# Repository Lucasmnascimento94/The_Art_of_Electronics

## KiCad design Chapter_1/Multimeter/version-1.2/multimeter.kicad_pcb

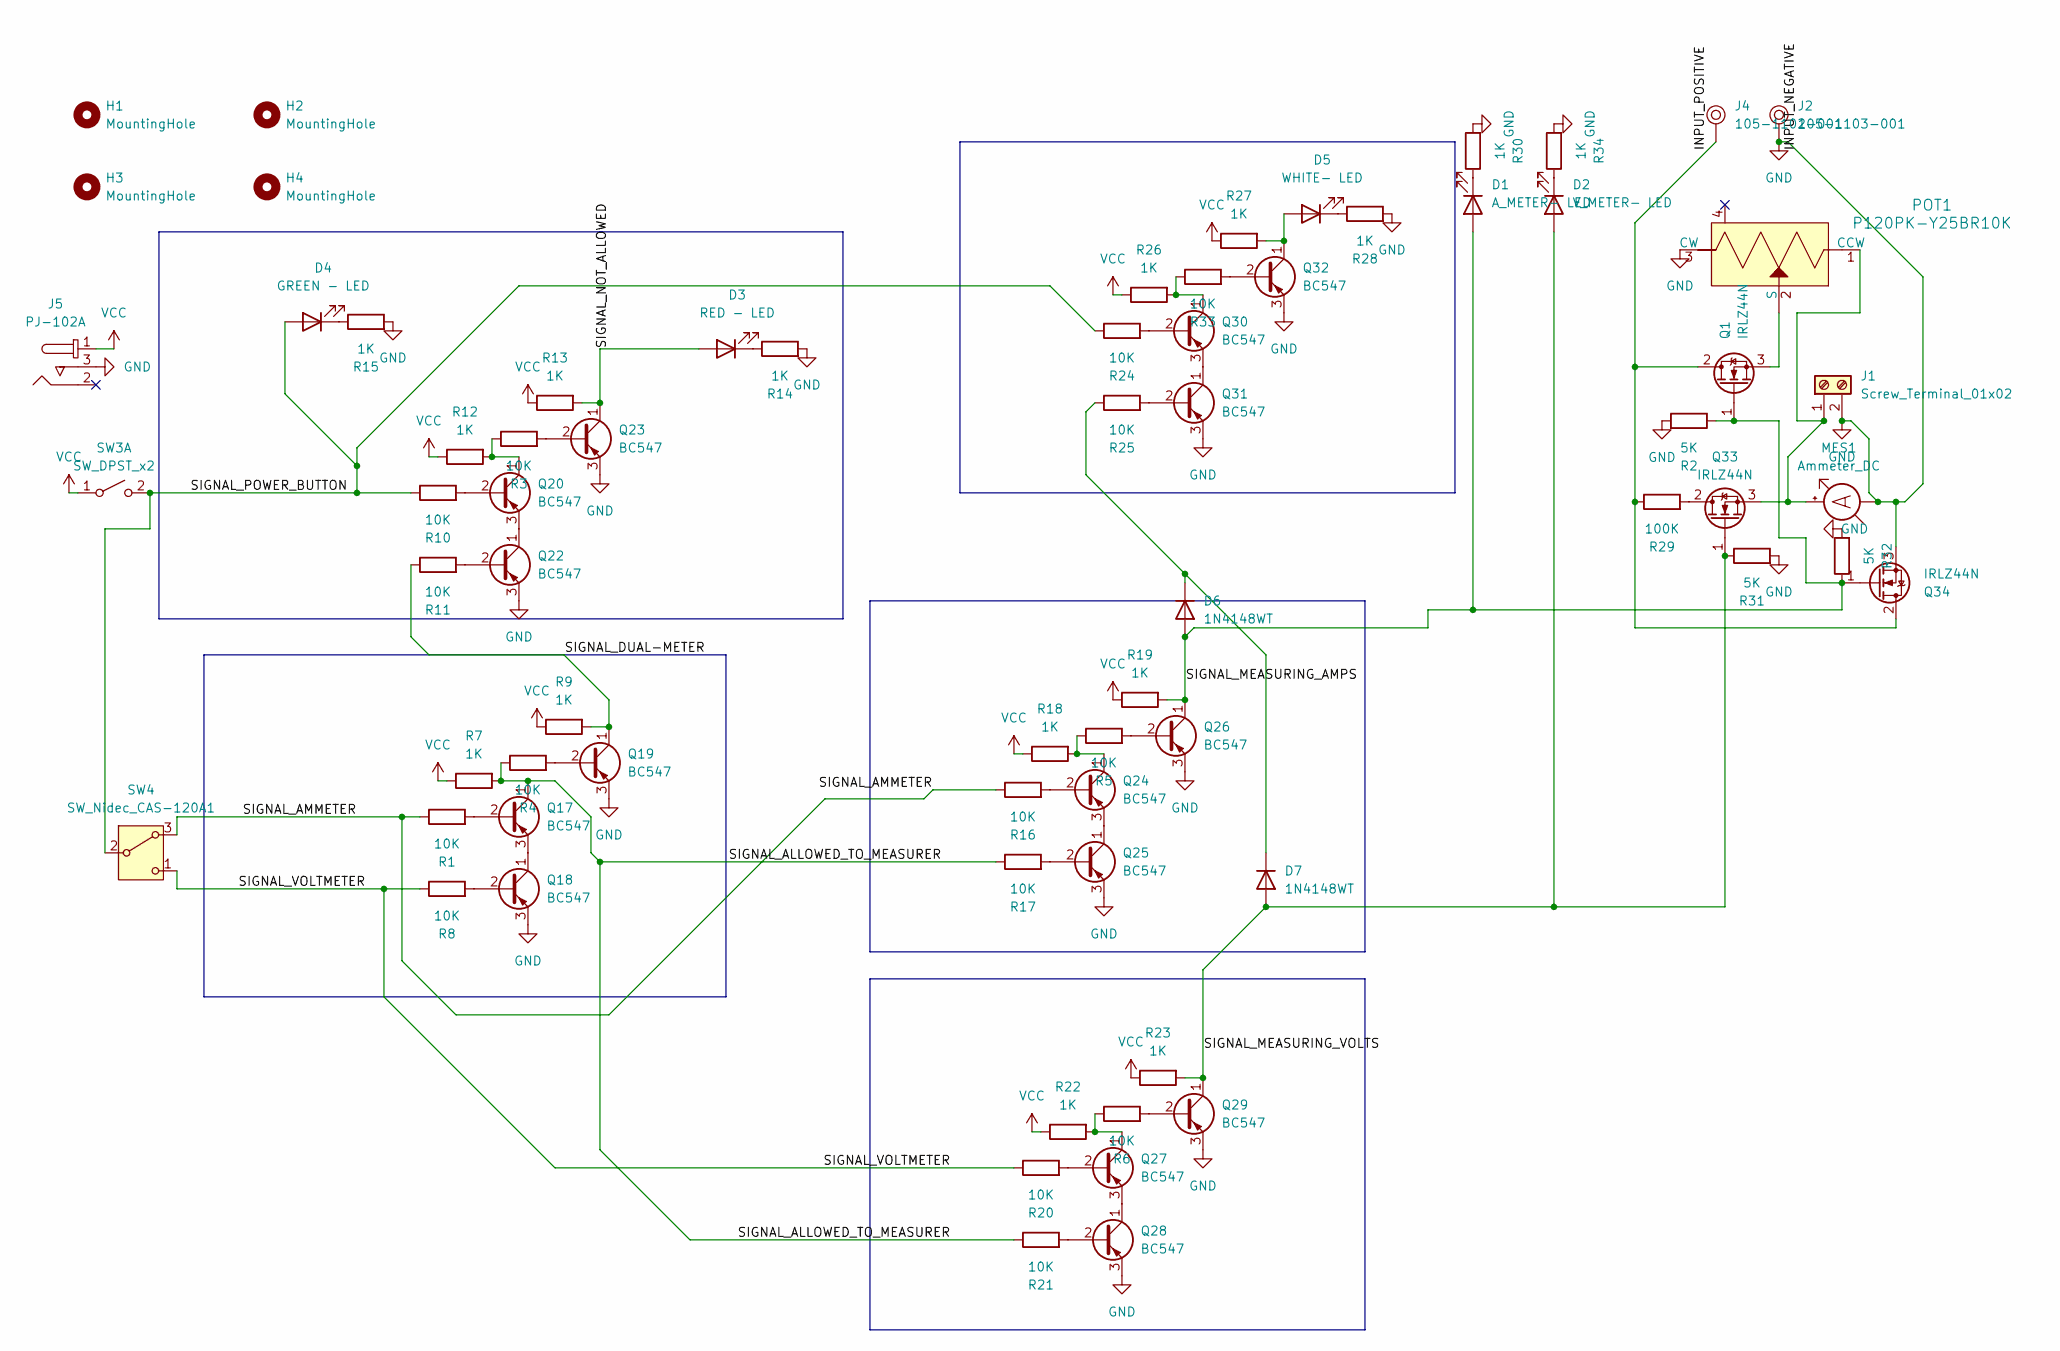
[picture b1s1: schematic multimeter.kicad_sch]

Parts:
D1: A_METER- LED; LED_D1.8mm_W3.3mm_H2.4mm
D2: V_METER- LED; LED_D1.8mm_W3.3mm_H2.4mm
D3: RED - LED; LED_D1.8mm_W3.3mm_H2.4mm
D4: GREEN - LED; LED_D1.8mm_W3.3mm_H2.4mm
D5: WHITE- LED; LED_D1.8mm_W3.3mm_H2.4mm
D6, D7: 1N4148WT; D_5W_P12.70mm_Horizontal
H1, H2, H3, H4: MountingHole; MountingHole_3.2mm_M3
J1: Screw_Terminal_01x02; TerminalBlock_MaiXu_MX126-5.0-02P_1x02_P5.00mm
J2: 105-1103-001; Test_Jack_Horiz; MPN 105-1103-001; Digi-Key_PN J577-ND
J4: 105-1102-001; Test_Jack_Horiz; MPN 105-1102-001; Digi-Key_PN J576-ND
J5: PJ-102A; Barrel_Jack_5.5mmODx2.1mmID_PJ-102A; MPN PJ-102A; Digi-Key_PN CP-102A-ND
MES1: Ammeter_DC
POT1: P120PK-Y25BR10K; Potentiometer_P120PK-Y25BR10K; MPN P120PK-Y25BR10K; Digi-Key_PN 987-1710-ND
Q1, Q33, Q34: IRLZ44N; TO-220-3_Vertical
Q17, Q18, Q19, Q20, Q22, Q23, Q24, Q25, Q26, Q27, Q28, Q29, Q30, Q31, Q32: BC547; TO-92_HandSolder
R1, R3, R4, R5, R6, R8, R10, R11, R16, R17, R20, R21, R24, R25, R33: 10K; R_Axial_DIN0207_L6.3mm_D2.5mm_P10.16mm_Horizontal
R2, R31, R32: 5K; R_Axial_DIN0207_L6.3mm_D2.5mm_P10.16mm_Horizontal
R7, R9, R12, R13, R14, R15, R18, R19, R22, R23, R26, R27, R28, R30, R34: 1K; R_Axial_DIN0207_L6.3mm_D2.5mm_P10.16mm_Horizontal
R29: 100K; R_Axial_DIN0207_L6.3mm_D2.5mm_P10.16mm_Horizontal
SW3: SW_DPST_x2; SW_DIP_SPSTx01_Piano_10.8x4.1mm_W7.62mm_P2.54mm
SW4: SW_Nidec_CAS-120A1; Switch_Toggle_ATE1D-2M3-10-Z

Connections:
/INPUT_POSITIVE: J4.1, Q1.2 (D), Q34.2 (D), R29.1
/SIGNAL_ALLOWED_TO_MEASURER: Q17.1 (C), R4.1, R7.2, R17.1, R21.1
/SIGNAL_AMMETER: R1.1, R16.1, SW4.3 (A)
/SIGNAL_DUAL-METER: Q19.1 (C), R9.2, R11.1
/SIGNAL_MEASURING_AMPS: D1.2 (A), D6.2 (A), Q1.1 (G), Q26.1 (C), Q34.1 (G), R2.1, R19.2, R32.1
/SIGNAL_MEASURING_VOLTS: D2.2 (A), D7.2 (A), Q29.1 (C), Q33.1 (G), R23.2, R31.1
/SIGNAL_NOT_ALLOWED: D3.2 (A), Q23.1 (C), R13.2
/SIGNAL_POWER_BUTTON: D4.2 (A), R10.1, R24.1, SW3.2 (B), SW4.2 (B)
/SIGNAL_VOLTMETER: R8.1, R20.1, SW4.1 (C)
GND: J1.2, J2.1, J5.3, MES1.1 (-), POT1.3 (CW), Q18.3 (E), Q19.3 (E), Q22.3 (E), Q23.3 (E), Q25.3 (E), Q26.3 (E), Q28.3 (E), Q29.3 (E), Q31.3 (E), Q32.3 (E), Q34.3 (S), R2.2, R14.2, R15.2, R28.2, R30.2, R31.2, R32.2, R34.2; also elsewhere on the board
unnamed: D1.1 (K), R30.1
unnamed: D2.1 (K), R34.1
unnamed: D3.1 (K), R14.1
unnamed: D4.1 (K), R15.1
unnamed: D5.2 (A), Q32.1 (C), R27.2
unnamed: D5.1 (K), R28.1
unnamed: D6.1 (K), D7.1 (K), R25.1
unnamed 17: J1.1, MES1.2 (+), POT1.1 (CCW), Q33.3 (S); also elsewhere on the board
unnamed 18: POT1.2 (S), Q1.3 (S); also elsewhere on the board
unnamed: Q17.2 (B), R1.2
unnamed: Q17.3 (E), Q18.1 (C)
unnamed: Q18.2 (B), R8.2
unnamed: Q19.2 (B), R4.2
unnamed: Q20.2 (B), R10.2
unnamed: Q20.1 (C), R3.1, R12.2
unnamed: Q20.3 (E), Q22.1 (C)
unnamed: Q22.2 (B), R11.2
unnamed: Q23.2 (B), R3.2
unnamed: Q24.2 (B), R16.2
unnamed: Q24.1 (C), R5.1, R18.2
unnamed: Q24.3 (E), Q25.1 (C)
unnamed: Q25.2 (B), R17.2
unnamed: Q26.2 (B), R5.2
unnamed: Q27.2 (B), R20.2
unnamed: Q27.1 (C), R6.1, R22.2
unnamed: Q27.3 (E), Q28.1 (C)
unnamed: Q28.2 (B), R21.2
unnamed: Q29.2 (B), R6.2
unnamed: Q30.2 (B), R24.2
unnamed: Q30.1 (C), R26.2, R33.1
unnamed: Q30.3 (E), Q31.1 (C)
unnamed: Q31.2 (B), R25.2
unnamed: Q32.2 (B), R33.2
unnamed: Q33.2 (D), R29.2
VCC: J5.1, R7.1, R9.1, R12.1, R13.1, R18.1, R19.1, R22.1, R23.1, R26.1, R27.1, SW3.1 (A)

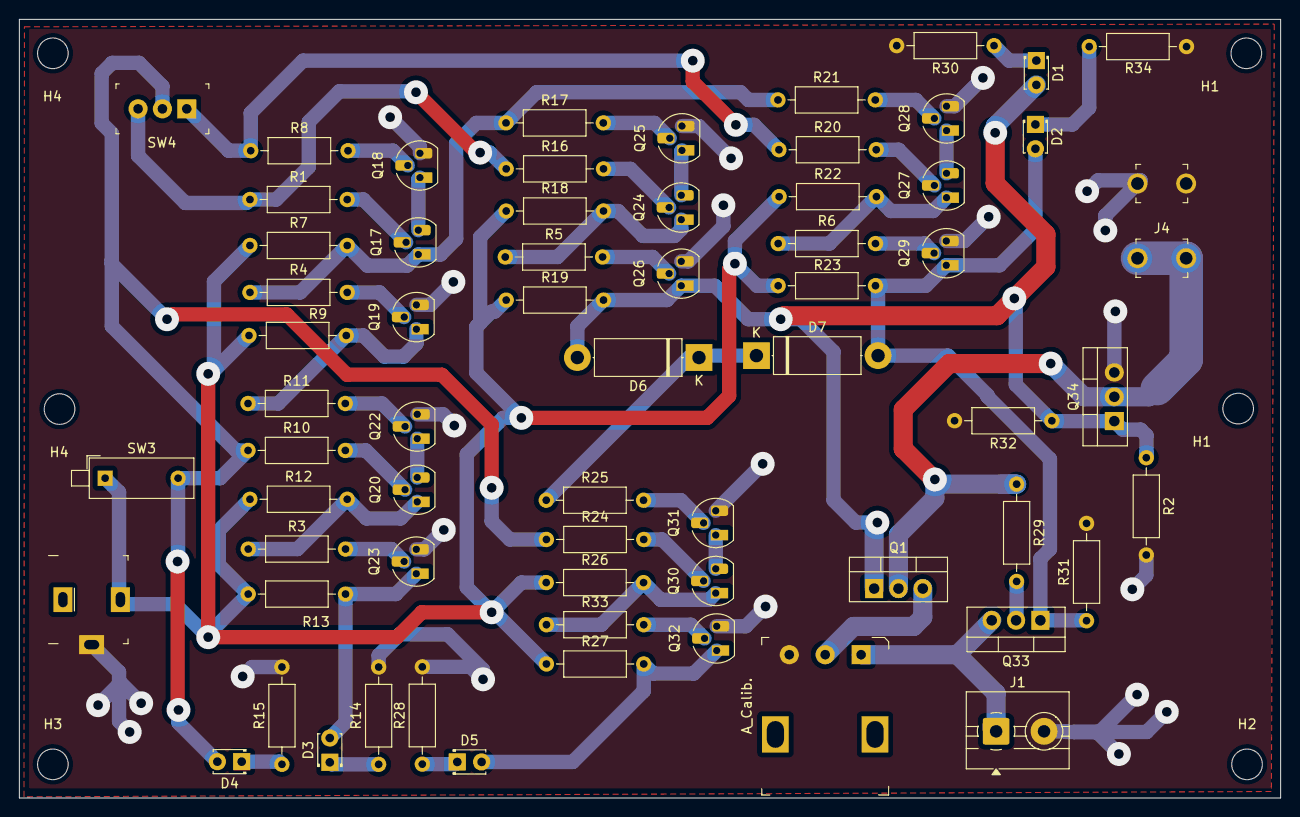
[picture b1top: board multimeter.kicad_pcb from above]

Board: 2 copper layers, 131.7 x 81.3 mm, 72 parts (0 on the bottom side), 45 nets.

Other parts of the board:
A_Calib.: P120PK-Y25BR10K; Potentiometer_P120PK-Y25BR10K
H1#2, H4#2: MountingHole; MountingHole_3.2mm_M3

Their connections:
GND: A_Calib..3 (CW); also elsewhere on the board
unnamed 17: A_Calib..1 (CCW); also elsewhere on the board
unnamed 18: A_Calib..2 (S); also elsewhere on the board

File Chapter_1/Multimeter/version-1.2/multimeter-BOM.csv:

"Id;""Designator"";""Footprint"";""Quantity"";""Designation"";""Supplier and ref"";",,,,,,,,,,,,,,
"1;""SW4"";""Switch_Toggle_ATE1D-2M3-10-Z"";1;""SW_Nidec_CAS-120A1"";;;",,,,,,,,,,,,,,
"2;""R32",R2,"R31"";""R_Axial_DIN0207_L6.3mm_D2.5mm_P10.16mm_Horizontal"";3;""5K"";;;",,,,,,,,,,,,
"3;""R5",R10,R6,R25,R16,R17,R33,R4,R20,R3,R21,R24,R1,R11,"R8"";""R_Axial_DIN0207_L6.3mm_D2.5mm_P10.16mm_Horizontal"";15;""10K"";;;"
"4;""Q30",Q31,Q25,Q29,Q20,Q28,Q26,Q19,Q22,Q27,Q18,Q17,Q32,Q24,"Q23"";""TO-92_HandSolder"";15;""BC547"";;;"
"5;""Q1",Q33,"Q34"";""TO-220-3_Vertical"";3;""IRLZ44N"";;;",,,,,,,,,,,,
"6;""D3"";""LED_D1.8mm_W3.3mm_H2.4mm"";1;""RED - LED"";;;",,,,,,,,,,,,,,
"7;""R30",R14,R12,R19,R27,R34,R28,R22,R23,R18,R13,R7,R15,R9,"R26"";""R_Axial_DIN0207_L6.3mm_D2.5mm_P10.16mm_Horizontal"";15;""1K"";;;"
"8;""J2"";""Test_Jack_Horiz"";1;""105-1103-001"";;;",,,,,,,,,,,,,,
"9;""J1"";""TerminalBlock_MaiXu_MX126-5.0-02P_1x02_P5.00mm"";1;""Screw_Terminal_01x02"";;;",,,,,,,,,,,,,,
"10;""D5"";""LED_D1.8mm_W3.3mm_H2.4mm"";1;""WHITE- LED"";;;",,,,,,,,,,,,,,
"11;""D6","D7"";""D_5W_P12.70mm_Horizontal"";2;""1N4148WT"";;;",,,,,,,,,,,,,
"12;""A_Calib."";""Potentiometer_P120PK-Y25BR10K"";1;""P120PK-Y25BR10K"";;;",,,,,,,,,,,,,,
"13;""J4"";""Test_Jack_Horiz"";1;""105-1102-001"";;;",,,,,,,,,,,,,,
"14;""D1"";""LED_D1.8mm_W3.3mm_H2.4mm"";1;""A_METER- LED"";;;",,,,,,,,,,,,,,
"15;""R29"";""R_Axial_DIN0207_L6.3mm_D2.5mm_P10.16mm_Horizontal"";1;""100K"";;;",,,,,,,,,,,,,,
"16;""SW3"";""SW_DIP_SPSTx01_Piano_10.8x4.1mm_W7.62mm_P2.54mm"";1;""SW_DPST_x2"";;;",,,,,,,,,,,,,,
"17;""D2"";""LED_D1.8mm_W3.3mm_H2.4mm"";1;""V_METER- LED"";;;",,,,,,,,,,,,,,
"18;""D4"";""LED_D1.8mm_W3.3mm_H2.4mm"";1;""GREEN - LED"";;;",,,,,,,,,,,,,,
"19;""J5"";""Barrel_Jack_5.5mmODx2.1mmID_PJ-102A"";1;""PJ-102A"";;;",,,,,,,,,,,,,,

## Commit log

2025-06-19 Corrected design
2025-06-19 continuing layout
2025-06-19 final
2025-06-19 gerber
2025-06-21 version-1.2 added
2025-06-21 final version1.2
2025-06-21 ProtoBoard Photo
2025-06-21 pcb adjusted size
